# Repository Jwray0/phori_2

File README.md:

# PhobGCCv2-HW fork
Seperate repository for the hardware used in the phori v2

The PhobGCC v2.0 board is licensed under CERN Open Hardware Licence Version 2 - Strongly Reciprocal.
This means that any changes made to the board should be made public and CHANGES.txt be updated to reflect said changes.

phori v2 is developed for the hori gamecube controller. 

https://github.com/PhobGCC/PhobGCCv2-HW

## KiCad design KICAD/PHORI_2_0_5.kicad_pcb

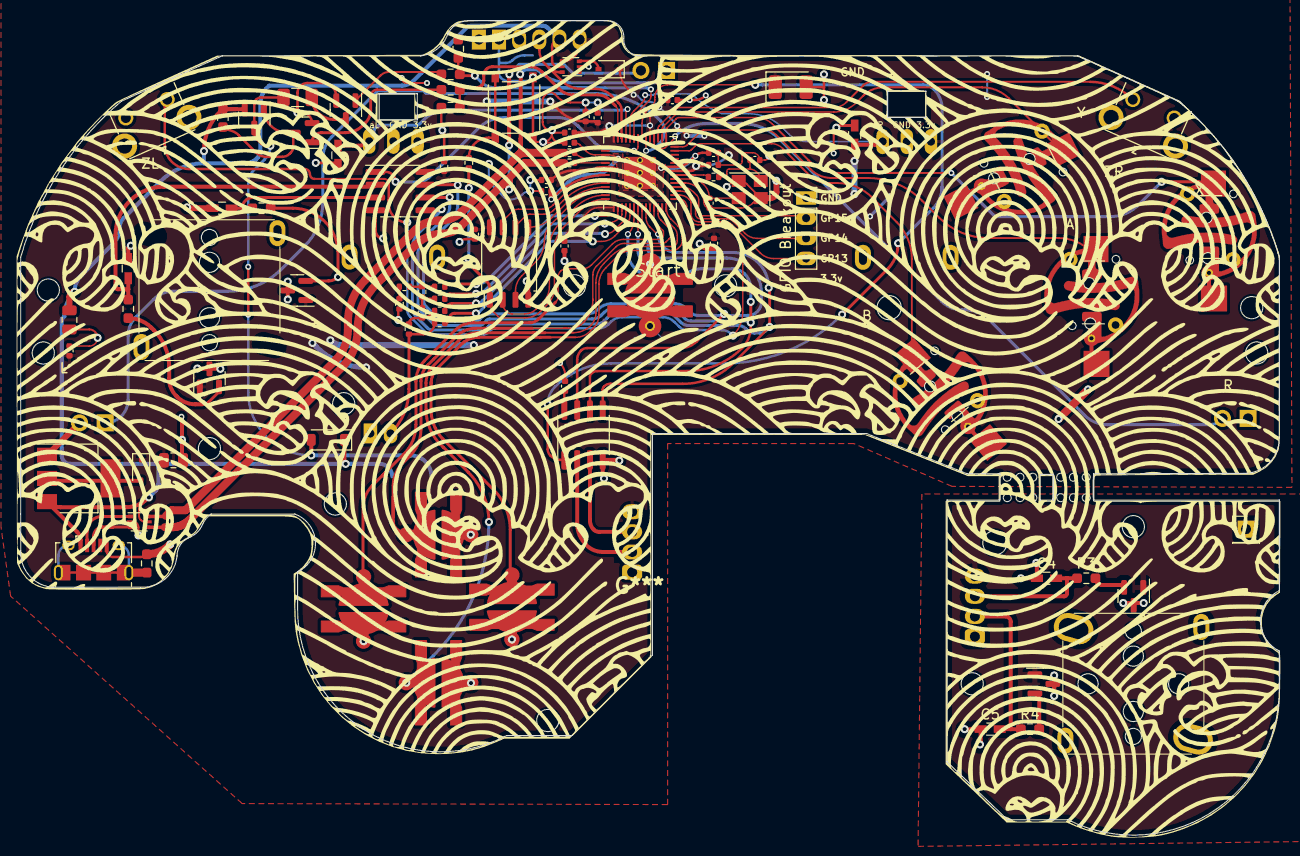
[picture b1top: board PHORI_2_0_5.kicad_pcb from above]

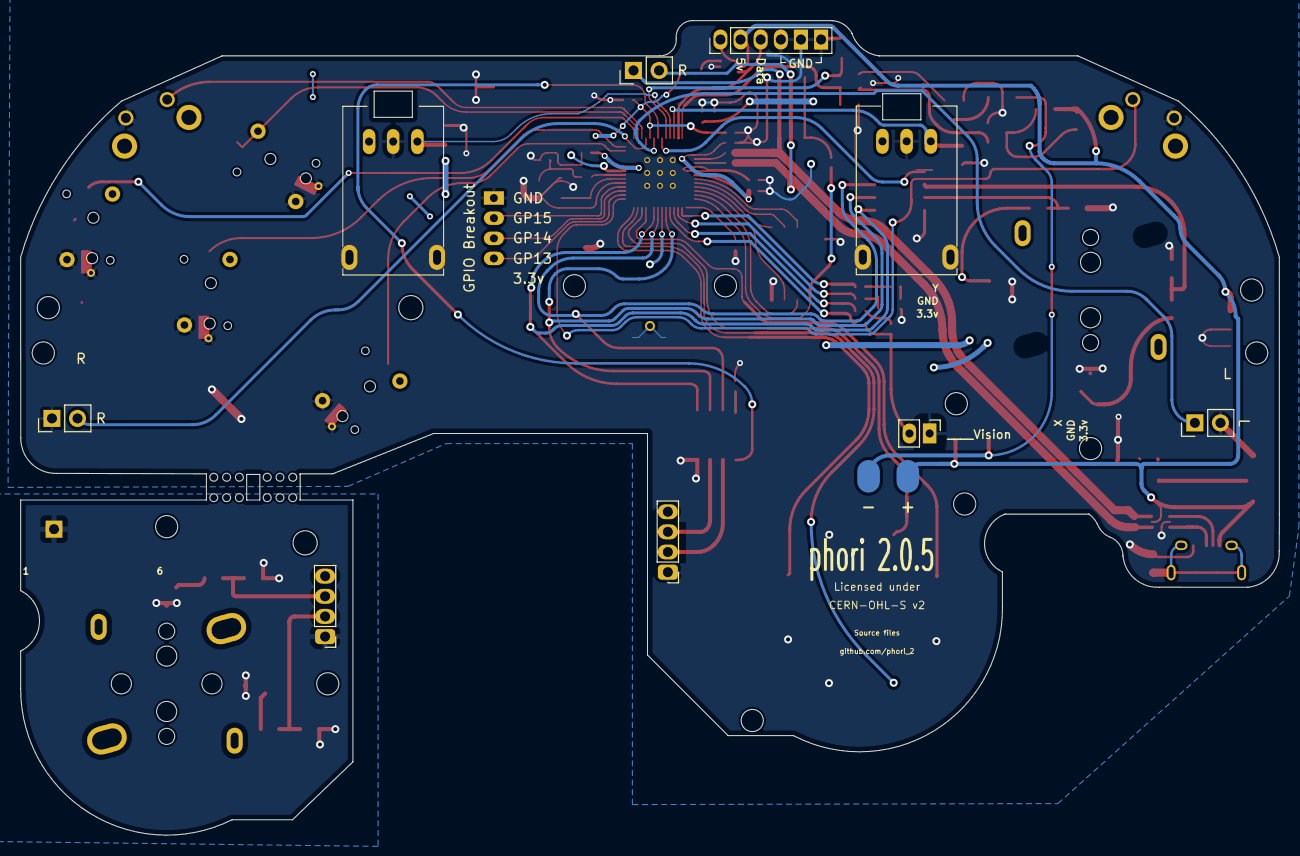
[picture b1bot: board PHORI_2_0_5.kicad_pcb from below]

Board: 2 copper layers, 125.0 x 80.9 mm, 113 parts (12 on the bottom side), 74 nets.

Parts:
C1: 47u; CP_EIA-3528-12_Kemet-T
C3, C4, C5, C6, C7, C8: 0.047u; C_0603_HandSoldering
C14, C15: 27p; C_0402_1005Metric
C16, C18: 10u; C_0805_2012Metric
C17, C19, C20, C22, C24, C25, C26, C27, C28, C29, C30, C31, C32: 100n; C_0402_1005Metric
C21, C23: 1u; C_0402_1005Metric
D1, D5: CUS10S30,H3F; D_SOD-323
D2: M7C; D_SOD-123
F1: Fuse; Fuse_1206_3216Metric
H5, H6: 1.8mm; MountingHole_1.8mm
H7, H7#2: 2.4mm; MountingHole_2.4mm
H8, H8#2, H8#3, H8#4, H8#5, H8#6, H8#7, H9: 2.2mm; MountingHole_2.2mm
H10, H10#2: MountingHole; MountingHole_1.8mm
H12, H13: MountingHole; MountingHole_2.0mm
H14, H15: MouseBite; breakaway-mousebites-double
J1: Conn_01x06_Female; GCC_Header_Straight_1x06_Pitch2.00mm
J2: Conn_01x02; PinHeader_1x02_P2.00mm_Vertical
J2#2: Conn_01x04_Female; PinHeader_1x04_P2.00mm_Vertical
J4: Conn_01x01; PinHeader_1x01_P2.54mm_Vertical
J4#2: Conn_01x04_Male; PinHeader_1x04_P2.00mm_Vertical
J5: Rumble; rumble_pins
J6: PinSocket_1x04_P2.00mm_Vertical
J9: USB_B_Micro; USB_Micro-B_Amphenol_10118194_Horizontal
Q1, Q3: Q_NMOS_GSD; SOT-23
Q2: Q_PMOS_GDS; SOT-23
R1, R2, R7, R8, R9: 180; R_0402_1005Metric
R3, R4, R5, R6: 2k; R_0603_1608Metric_Pad0.98x0.95mm_HandSolder
R10, R19, R24, R25: 316; R_0402_1005Metric
R11, R12: 100R; R_0603_1608Metric_Pad0.98x0.95mm_HandSolder
R13, R14, R15: 10k; R_0603_1608Metric_Pad0.98x0.95mm_HandSolder
R16, R18: 1k; R_0402_1005Metric
R17: 100k; R_0603_1608Metric_Pad0.98x0.95mm_HandSolder
R20, R21: 27; R_0402_1005Metric
RV1, RV2: R_POT_MountingPin; GCC_Slider
S1: BOOTSEL; SW_TS-1187A-B-A-B
SW1, SW1#2: A; ABXY_Contact_Omron_Switch_b3F
SW2: B; ABXY_Contact_Omron_Switch_b3F_v2
SW4: Y; ABXY_Contact_Omron_Switch_b3F_v2
SW5: Start; Dpad_Contact_TL3315NF_2
SW6: L; Pin_Header_Straight_1x02_Pitch2.54mm
SW7, SW7#2: R; Pin_Header_Straight_1x02_Pitch2.54mm
SW8, SW8#2: Z; Z_Switch_Edge_Omron
SW10, SW10#2: Dup; Dpad_Contact_TL3315NF_2
SW11, SW11#2: Dright; Dpad_Contact_TL3315NF_2
U1, U1#2: MCP3002; SOIC-8_3.9x4.9mm_P1.27mm
U2: Stickbox_Assembly_Main; GCC_Stickbox_Hall_Only
U3, U4, U10, U11: DRV5055Z3QDBZT; SOT-23
U5: Stickbox_Assembly; GCC_Stickbox_Hall_Only
U6: AMS1117-3.3; SOT-223-3_TabPin2
U7: W25Q128JVS; SOIC-8_5.23x5.23mm_P1.27mm
U8: RP2040; RP2040-QFN-56
U12, U13: USBLC6-2P6; SOT-666
Y1: Crystal_GND24; Crystal_SMD_3225-4Pin_3.2x2.5mm

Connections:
+1V1: C19.1, C20.1, C21.1, U8.23 (DVDD), U8.45 (VREG_VOUT), U8.50 (DVDD)
+3V3: C1.1, C17.1, C18.1, C22.1, C23.1, C24.1, C25.1, C26.1, C27.1, C28.1, C29.1, C30.1, C31.1, D1.1 (K), D5.1 (K), J1.1, J2#2.4, RV1.1 (V+), RV2.1 (V+), U1#2.8 (VDD/VREF), U3.1 (VCC), U4.1 (VCC), U7.8 (VCC), U8.1 (IOVDD), U8.10 (IOVDD), U8.22 (IOVDD), U8.33 (IOVDD), U8.42 (IOVDD), U8.43 (ADC_AVDD), U8.44 (VREG_IN), U8.48 (USB_VDD), U8.49 (IOVDD), U13.4
+5V: C16.1, D2.1 (K), J1.2, J5.1, J9.1, Q2.2 (S), R13.2, U6.3 (VI), U12.5, U13.5
A: SW1#2.1, U8.28 (GPIO17)
B: SW2.1, U8.27 (GPIO16)
Brake: R12.1, R14.2, U8.41 (GPIO29_ADC3)
CLK: U1.7 (CLK), U1#2.7 (CLK), U8.8 (GPIO6)
CS1: U1#2.1 (~CS/SHDN), U8.36 (GPIO24)
CS2: U1.1 (~CS/SHDN), U8.35 (GPIO23)
C_X_Filt: C5.1, R4.1
C_Y_Filt: C4.1, J4#2.3, R3.1
Ddown: SW10#2.1, U8.13 (GPIO10)
Din: U1.5 (DIN), U1#2.5 (DIN), U8.9 (GPIO7)
Dleft: SW11.1, U8.11 (GPIO8)
Dout: U1.e (DOUT), U1#2.6 (DOUT), U8.6 (GPIO4)
Dright: SW11#2.1, U8.14 (GPIO11)
Dup: SW10.1, U8.12 (GPIO9)
GCC_DATA: J1.3, U8.40 (GPIO28_ADC2), U13.6
GND: C1.2, C3.2, C6.2, C7.2, C8.2, C14.2, C16.2, C17.2, C18.2, C19.2, C20.2, C21.2, C22.2, C23.2, C24.2, C25.2, C26.2, C27.2, C28.2, C29.2, C30.2, C31.2, C32.2, J1.4, J1.5, J1.6, J2.1, J2#2.1, J6.1, J9.5, Q1.2 (S), Q3.2 (S), R1.2, R14.1, R15.1, R17.2, RV1.2 (GND), RV2.2 (GND), S1.A, S1.B, SW1.2, SW1#2.2, SW2.2, SW4.2, SW5.2, SW5.3, SW6.2, SW7#2.1, SW8.2, SW8#2.1, SW10.2, SW10#2.2, SW11.2, SW11#2.2, U1.4 (VSS), U3.3 (GND), U4.3 (GND), U6.1 (GND), U7.4 (GND), U8.19 (TESTEN), U8.57 (GND), U12.2, U13.2, Y1.2, Y1.4
GPIO13: J6.4, U8.16 (GPIO13)
GPIO14: J6.3, U8.17 (GPIO14)
GPIO15: J6.2, U8.18 (GPIO15)
H1XS: R6.2, U4.2 (OUT)
H1YS: R5.2, U3.2 (OUT)
H2XS: R4.2, U10.2 (OUT)
H2YS: R3.2, U11.2 (OUT)
L: SW6.1, U8.34 (GPIO22)
Ladder1: R10.2, U8.2 (GPIO0)
Ladder2: R19.2, U8.3 (GPIO1)
Ladder3: R24.2, U8.4 (GPIO2)
Ladder4: R25.2, U8.5 (GPIO3)
Lanalog: C7.1, RV1.3 (Signal), U8.39 (GPIO27_ADC1)
LeftZ: SW8#2.2, U8.15 (GPIO12)
unnamed: R18.2, Y1.1
unnamed: D1.2 (A), U6.2 (VO)
unnamed: D2.2 (A), J5.2, Q2.3 (D)
unnamed: D5.2 (A), U13.3
unnamed: F1.2, Q3.3 (D)
unnamed: J9.6, R17.1
unnamed: Q1.1 (G), R12.2
unnamed: Q1.3 (D), Q2.1 (G), R13.1
unnamed: Q3.1 (G), R11.2
unnamed: R1.1, R2.2
unnamed: R2.1, R7.2, R10.1
unnamed: R7.1, R8.2, R19.1
unnamed: R20.2, U8.47 (USB_DP)
unnamed: R21.2, U8.46 (USB_DM)
unnamed: R8.1, R9.2, R24.1
QSPI_SCLK: U7.6 (CLK), U8.52 (QSPI_SCLK)
QSPI_SD0: U7.5 (DI(IO0)), U8.53 (QSPI_SD0)
QSPI_SD1: U7.2 (DO(IO1)), U8.55 (QSPI_SD1)
QSPI_SD2: U7.3 (IO2), U8.54 (QSPI_SD2)
QSPI_SD3: U7.7 (IO3), U8.51 (QSPI_SD3)
QSPI_SS: R16.1, U7.1 (~CS), U8.56 (QSPI_SS)
R: SW7#2.2, U8.32 (GPIO21)
Ranalog: C3.1, RV2.3 (Signal), U8.38 (GPIO26_ADC0)
Rumble: R11.1, R15.2, U8.37 (GPIO25)
Start: SW5.1, U8.7 (GPIO5)
Stick_filt_x: C8.1, R6.1
Stick_filt_y: C6.1, R5.1
USB_BOOT: R16.2, S1.C, S1.D
USB_D+: R20.1, SW7.2, U12.4
USB_D+_Raw: J9.3, U12.3
USB_D-: R21.1, SW7.1, U12.6
USB_D-_Raw: J9.2, U12.1
V: J2.2, R9.1, R25.1
VCC: C32.1, U1.8 (VDD/VREF)
X: SW1.1, U8.29 (GPIO18)
XIN: C14.1, U8.20 (XIN), Y1.3
XOUT: R18.1, U8.21 (XOUT)
Y: SW4.1, U8.30 (GPIO19)
Z: SW8.1, U8.31 (GPIO20)
gnd: C4.2, C5.2, J4.1, J4#2.1, U10.3 (GND), U11.3 (GND)
vcc: J4#2.4, U10.1 (VCC), U11.1 (VCC)

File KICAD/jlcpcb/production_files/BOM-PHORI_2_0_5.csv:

Comment,Designator,Footprint,LCSC
"CUS10S30,H3F",D5,D_SOD-323,C146335
Q_PMOS_GDS,Q2,SOT-23,C15127
0.047u,"C3,C4,C5,C6,C7,C8",C_0603_HandSoldering,C1622
Q_NMOS_GSD,"Q1,Q3",SOT-23,C20917
100R,"R11,R12",R_0603_1608Metric_Pad0.98x0.95mm_HandSolder,C22775
2k,"R3,R4,R5,R6",R_0603_1608Metric_Pad0.98x0.95mm_HandSolder,C22975
100k,R17,R_0603_1608Metric_Pad0.98x0.95mm_HandSolder,C25803
10k,"R13,R14,R15",R_0603_1608Metric_Pad0.98x0.95mm_HandSolder,C25804
Fuse,F1,Fuse_1206_3216Metric,C69680
M7C,D2,D_SOD-123,C8598
100n,C31,C_0402_1005Metric,
180,R7,R_0402_1005Metric,
Conn_01x04_Male,J4,PinHeader_1x04_P2.00mm_Vertical,
316,R10,R_0402_1005Metric,
RP2040,U8,RP2040-QFN-56,
1u,C21,C_0402_1005Metric,
DRV5055Z3QDBZT,U10,SOT-23,
10u,C18,C_0805_2012Metric,
100n,C28,C_0402_1005Metric,
MCP3002,U1,SOIC-8_3.9x4.9mm_P1.27mm,
100n,C17,C_0402_1005Metric,
316,R19,R_0402_1005Metric,
1k,R16,R_0402_1005Metric,
USBLC6-2P6,U12,SOT-666,
100n,C22,C_0402_1005Metric,
180,R2,R_0402_1005Metric,
100n,C20,C_0402_1005Metric,
1u,C23,C_0402_1005Metric,
Z,SW8,Z_Switch_Edge_Omron,
W25Q128JVS,U7,SOIC-8_5.23x5.23mm_P1.27mm,
27,R21,R_0402_1005Metric,
100n,C29,C_0402_1005Metric,
180,R8,R_0402_1005Metric,
USBLC6-2P6,U13,SOT-666,
100n,C24,C_0402_1005Metric,
Crystal_GND24,Y1,Crystal_SMD_3225-4Pin_3.2x2.5mm,
100n,C32,C_0402_1005Metric,
180,R1,R_0402_1005Metric,
316,R25,R_0402_1005Metric,
27,R20,R_0402_1005Metric,
1k,R18,R_0402_1005Metric,
47u,C1,CP_EIA-3528-12_Kemet-T,
27p,C14,C_0402_1005Metric,
USB_B_Micro,J9,USB_Micro-B_Amphenol_10118194_Horizontal,
10u,C16,C_0805_2012Metric,
100n,C26,C_0402_1005Metric,
180,R9,R_0402_1005Metric,
100n,C19,C_0402_1005Metric,
100n,C27,C_0402_1005Metric,
BOOTSEL,S1,SW_TS-1187A-B-A-B,
AMS1117-3.3,U6,SOT-223-3_TabPin2,
DRV5055Z3QDBZT,U4,SOT-23,
316,R24,R_0402_1005Metric,
"CUS10S30,H3F",D1,D_SOD-323,
100n,C25,C_0402_1005Metric,
100n,C30,C_0402_1005Metric,
27p,C15,C_0402_1005Metric,
DRV5055Z3QDBZT,U11,SOT-23,
DRV5055Z3QDBZT,U3,SOT-23,
Conn_01x04_Female,J2,PinHeader_1x04_P2.00mm_Vertical,

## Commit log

2024-02-23 adding KiKad filed and JLC ordering
    Crude BOM and CPL
    Will need to clean up later
2024-02-23 updated back Silkscreen
2024-02-23 fixed stick placement
2024-02-23 Updated JLC files
2024-02-24 Better BOM
2024-02-24 push
2024-03-08 recent
2024-03-08 fixed stick hole
2024-03-08 added d+- holes
2024-04-05 Updated CPL
    Added updated CPL and Gerber for ordering at JLC
2024-04-05 Kikad
2024-04-26 KIKAD 8
    Kikad 8 update and some small fixes
2024-12-20 GND on Rp2040
2024-12-20 new gerber

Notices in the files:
KICAD/PHORI_2_0_5.kicad_pcb:
CERN-OHL-S v2
